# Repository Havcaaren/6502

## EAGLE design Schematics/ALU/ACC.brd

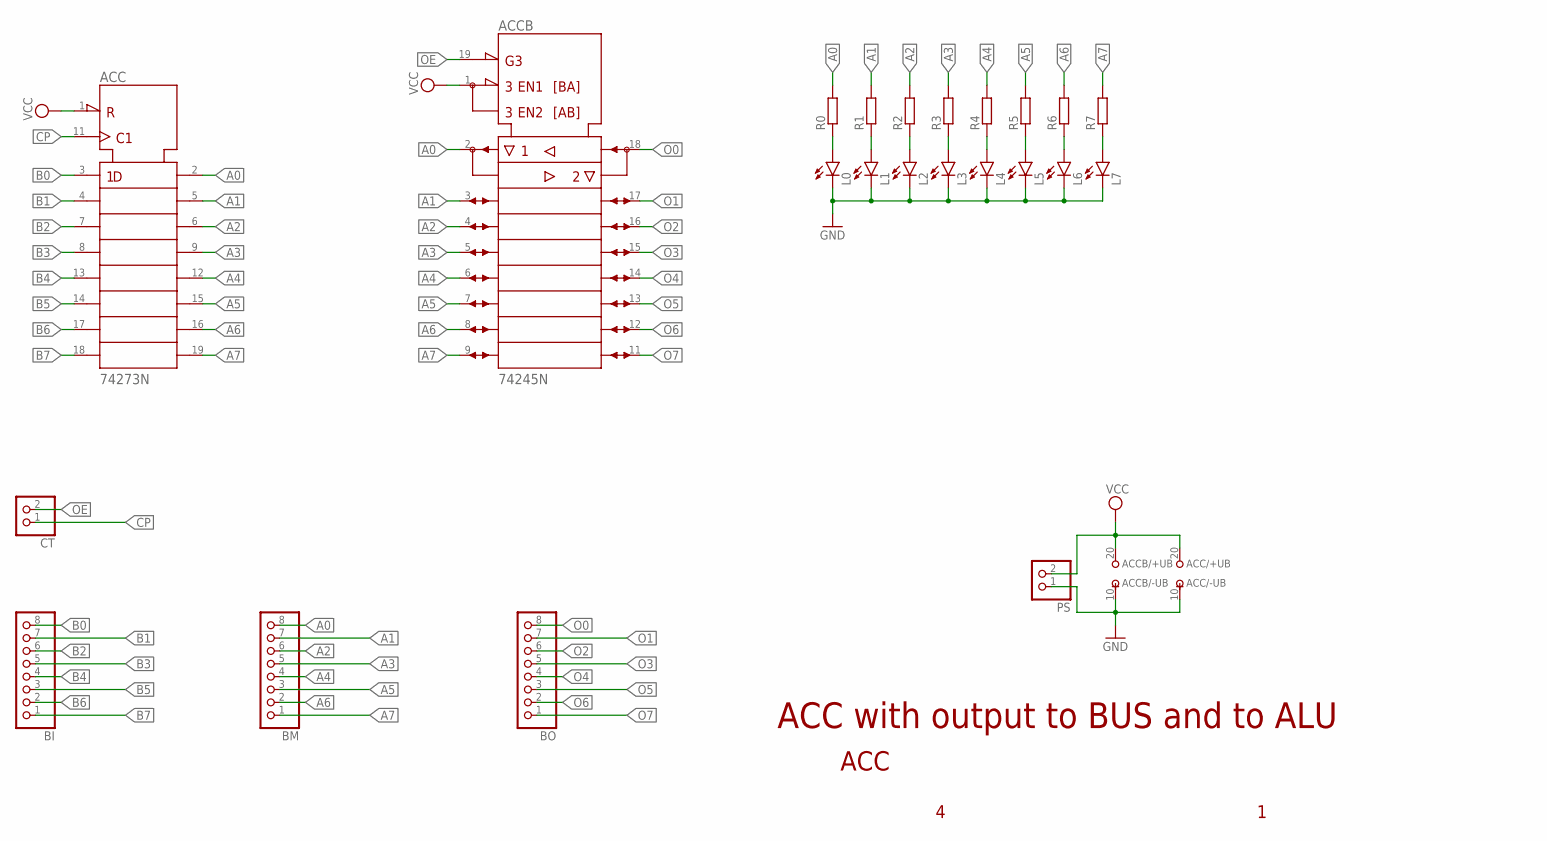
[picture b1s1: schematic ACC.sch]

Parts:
ACC: 74273N; DIL20
ACCB: 74245N; DIL20
BI: PINHD-1X8; 1X08
BM: PINHD-1X8; 1X08
BO: PINHD-1X8; 1X08
CT: PINHD-1X2; 1X02
L0, L1, L2, L3, L4, L5, L6, L7: LED5MM
PS: PINHD-1X2; 1X02
R0, R1, R2, R3, R4, R5, R6, R7: R-EU_0204/7; 0204/7

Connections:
A0: ACC.2 (1Q), ACCB.2 (A1), BM.8, R0.2
A1: ACC.5 (2Q), ACCB.3 (A2), BM.7, R1.2
A2: ACC.6 (3Q), ACCB.4 (A3), BM.6, R2.2
A3: ACC.9 (4Q), ACCB.5 (A4), BM.5, R3.2
A4: ACC.12 (5Q), ACCB.6 (A5), BM.4, R4.2
A5: ACC.15 (6Q), ACCB.7 (A6), BM.3, R5.2
A6: ACC.16 (7Q), ACCB.8 (A7), BM.2, R6.2
A7: ACC.19 (8Q), ACCB.9 (A8), BM.1, R7.2
B0: ACC.3 (1D), BI.8
B1: ACC.4 (2D), BI.7
B2: ACC.7 (3D), BI.6
B3: ACC.8 (4D), BI.5
B4: ACC.13 (5D), BI.4
B5: ACC.14 (6D), BI.3
B6: ACC.17 (7D), BI.2
B7: ACC.18 (8D), BI.1
CP: ACC.11 (CLK), CT.1
GND: ACC.10 (-UB), ACCB.10 (-UB), L0.K (C), L1.K (C), L2.K (C), L3.K (C), L4.K (C), L5.K (C), L6.K (C), L7.K (C), PS.1
unnamed: L0.A, R0.1
unnamed: L1.A, R1.1
unnamed: L2.A, R2.1
unnamed: L3.A, R3.1
unnamed: L4.A, R4.1
unnamed: L5.A, R5.1
unnamed: L6.A, R6.1
unnamed: L7.A, R7.1
O0: ACCB.18 (B1), BO.8
O1: ACCB.17 (B2), BO.7
O2: ACCB.16 (B3), BO.6
O3: ACCB.15 (B4), BO.5
O4: ACCB.14 (B5), BO.4
O5: ACCB.13 (B6), BO.3
O6: ACCB.12 (B7), BO.2
O7: ACCB.11 (B8), BO.1
OE: ACCB.19 (!G), CT.2
VCC: ACC.1 (!CLR), ACC.20 (+UB), ACCB.1 (DIR), ACCB.20 (+UB), PS.2

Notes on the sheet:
ACC with output to BUS and to ALU
ACC

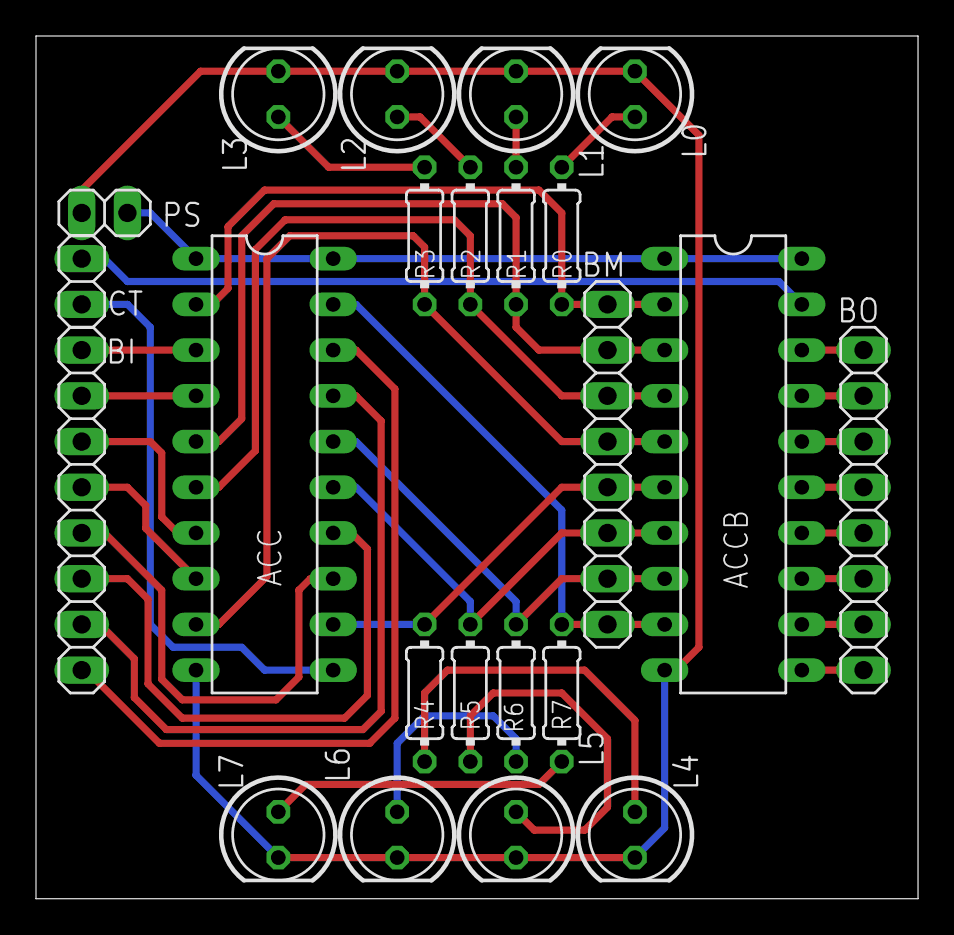
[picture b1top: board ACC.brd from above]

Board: 2 copper layers, 49.0 x 47.9 mm, 23 parts (0 on the bottom side), 36 nets.

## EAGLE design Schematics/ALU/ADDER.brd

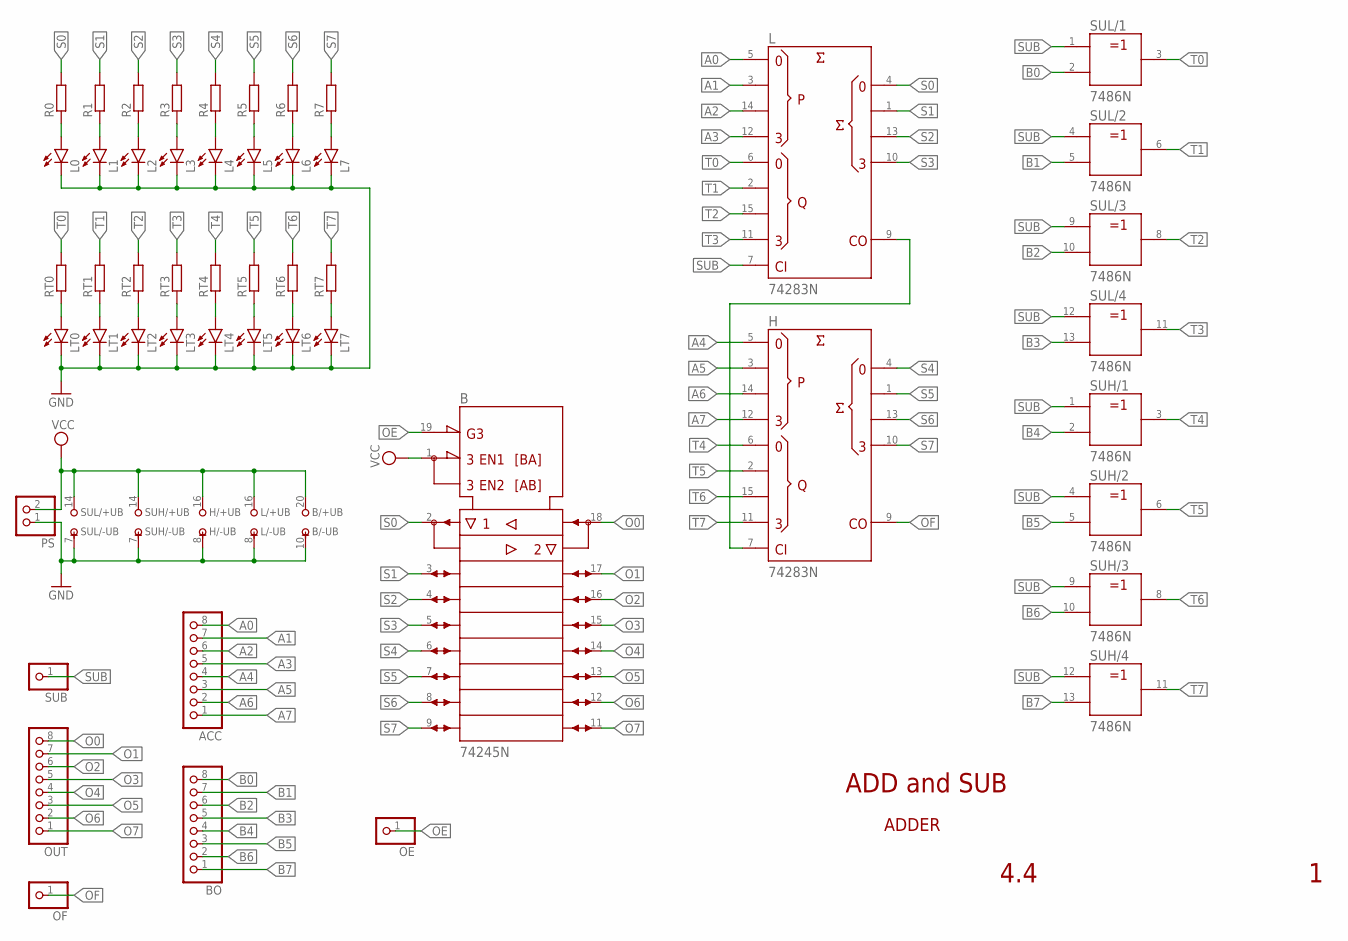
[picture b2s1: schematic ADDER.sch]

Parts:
ACC: PINHD-1X8; 1X08
B: 74245N; DIL20
BO: PINHD-1X8; 1X08
H: 74283N; DIL16
L: 74283N; DIL16
L0, L1, L2, L3, L4, L5, L6, L7: LED5MM
LT0, LT1, LT2, LT3, LT4, LT5, LT6, LT7: LED5MM
OE: PINHD-1X1; 1X01
OF: PINHD-1X1; 1X01
OUT: PINHD-1X8; 1X08
PS: PINHD-1X2; 1X02
R0, R1, R2, R3, R4, R5, R6, R7: R-EU_0204/7; 0204/7
RT0, RT1, RT2, RT3, RT4, RT5, RT6, RT7: R-EU_0204/7; 0204/7
SUB: PINHD-1X1; 1X01
SUH: 7486N; DIL14
SUL: 7486N; DIL14

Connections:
A0: ACC.8, L.5 (A1)
A1: ACC.7, L.3 (A2)
A2: ACC.6, L.14 (A3)
A3: ACC.5, L.12 (A4)
A4: ACC.4, H.5 (A1)
A5: ACC.3, H.3 (A2)
A6: ACC.2, H.14 (A3)
A7: ACC.1, H.12 (A4)
B0: BO.8, SUL.2 (B)
B1: BO.7, SUL.5 (B)
B2: BO.6, SUL.10 (B)
B3: BO.5, SUL.13 (B)
B4: BO.4, SUH.2 (B)
B5: BO.3, SUH.5 (B)
B6: BO.2, SUH.10 (B)
B7: BO.1, SUH.13 (B)
GND: B.10 (-UB), H.8 (-UB), L.8 (-UB), L0.K (C), L1.K (C), L2.K (C), L3.K (C), L4.K (C), L5.K (C), L6.K (C), L7.K (C), LT0.K (C), LT1.K (C), LT2.K (C), LT3.K (C), LT4.K (C), LT5.K (C), LT6.K (C), LT7.K (C), PS.1, SUH.7 (-UB), SUL.7 (-UB)
unnamed: H.7 (C0), L.9 (C4)
unnamed: L0.A, R0.1
unnamed: L1.A, R1.1
unnamed: L2.A, R2.1
unnamed: L3.A, R3.1
unnamed: L4.A, R4.1
unnamed: L5.A, R5.1
unnamed: L6.A, R6.1
unnamed: L7.A, R7.1
unnamed: LT0.A, RT0.1
unnamed: LT1.A, RT1.1
unnamed: LT2.A, RT2.1
unnamed: LT3.A, RT3.1
unnamed: LT4.A, RT4.1
unnamed: LT5.A, RT5.1
unnamed: LT6.A, RT6.1
unnamed: LT7.A, RT7.1
O0: B.18 (B1), OUT.8
O1: B.17 (B2), OUT.7
O2: B.16 (B3), OUT.6
O3: B.15 (B4), OUT.5
O4: B.14 (B5), OUT.4
O5: B.13 (B6), OUT.3
O6: B.12 (B7), OUT.2
O7: B.11 (B8), OUT.1
OE: B.19 (!G), OE.1
OF: H.9 (C4), OF.1
S0: B.2 (A1), L.4 (S1), R0.2
S1: B.3 (A2), L.1 (S2), R1.2
S2: B.4 (A3), L.13 (S3), R2.2
S3: B.5 (A4), L.10 (S4), R3.2
S4: B.6 (A5), H.4 (S1), R4.2
S5: B.7 (A6), H.1 (S2), R5.2
S6: B.8 (A7), H.13 (S3), R6.2
S7: B.9 (A8), H.10 (S4), R7.2
SUB: L.7 (C0), SUB.1, SUH.1 (A), SUH.4 (A), SUH.9 (A), SUH.12 (A), SUL.1 (A), SUL.4 (A), SUL.9 (A), SUL.12 (A)
T0: L.6 (B1), RT0.2, SUL.3 (Y)
T1: L.2 (B2), RT1.2, SUL.6 (Y)
T2: L.15 (B3), RT2.2, SUL.8 (Y)
T3: L.11 (B4), RT3.2, SUL.11 (Y)
T4: H.6 (B1), RT4.2, SUH.3 (Y)
T5: H.2 (B2), RT5.2, SUH.6 (Y)
T6: H.15 (B3), RT6.2, SUH.8 (Y)
T7: H.11 (B4), RT7.2, SUH.11 (Y)
VCC: B.1 (DIR), B.20 (+UB), H.16 (+UB), L.16 (+UB), PS.2, SUH.14 (+UB), SUL.14 (+UB)

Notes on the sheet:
ADD and SUB
ADDER
4.4

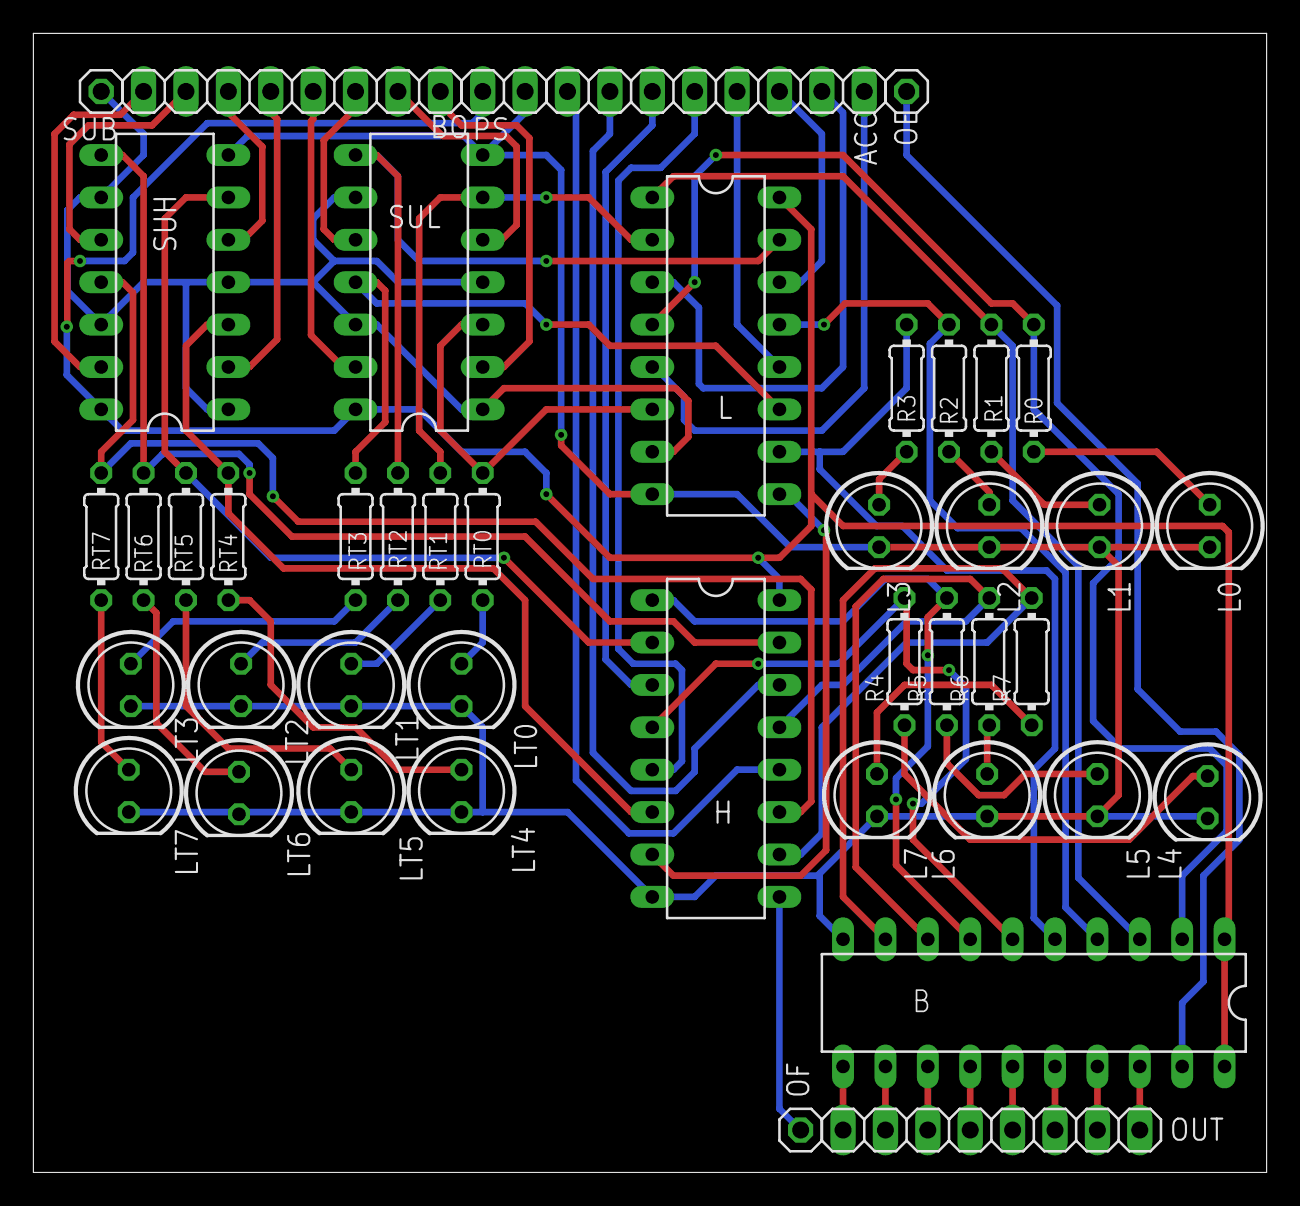
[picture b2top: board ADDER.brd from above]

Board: 2 copper layers, 73.9 x 68.2 mm, 44 parts (0 on the bottom side), 62 nets.

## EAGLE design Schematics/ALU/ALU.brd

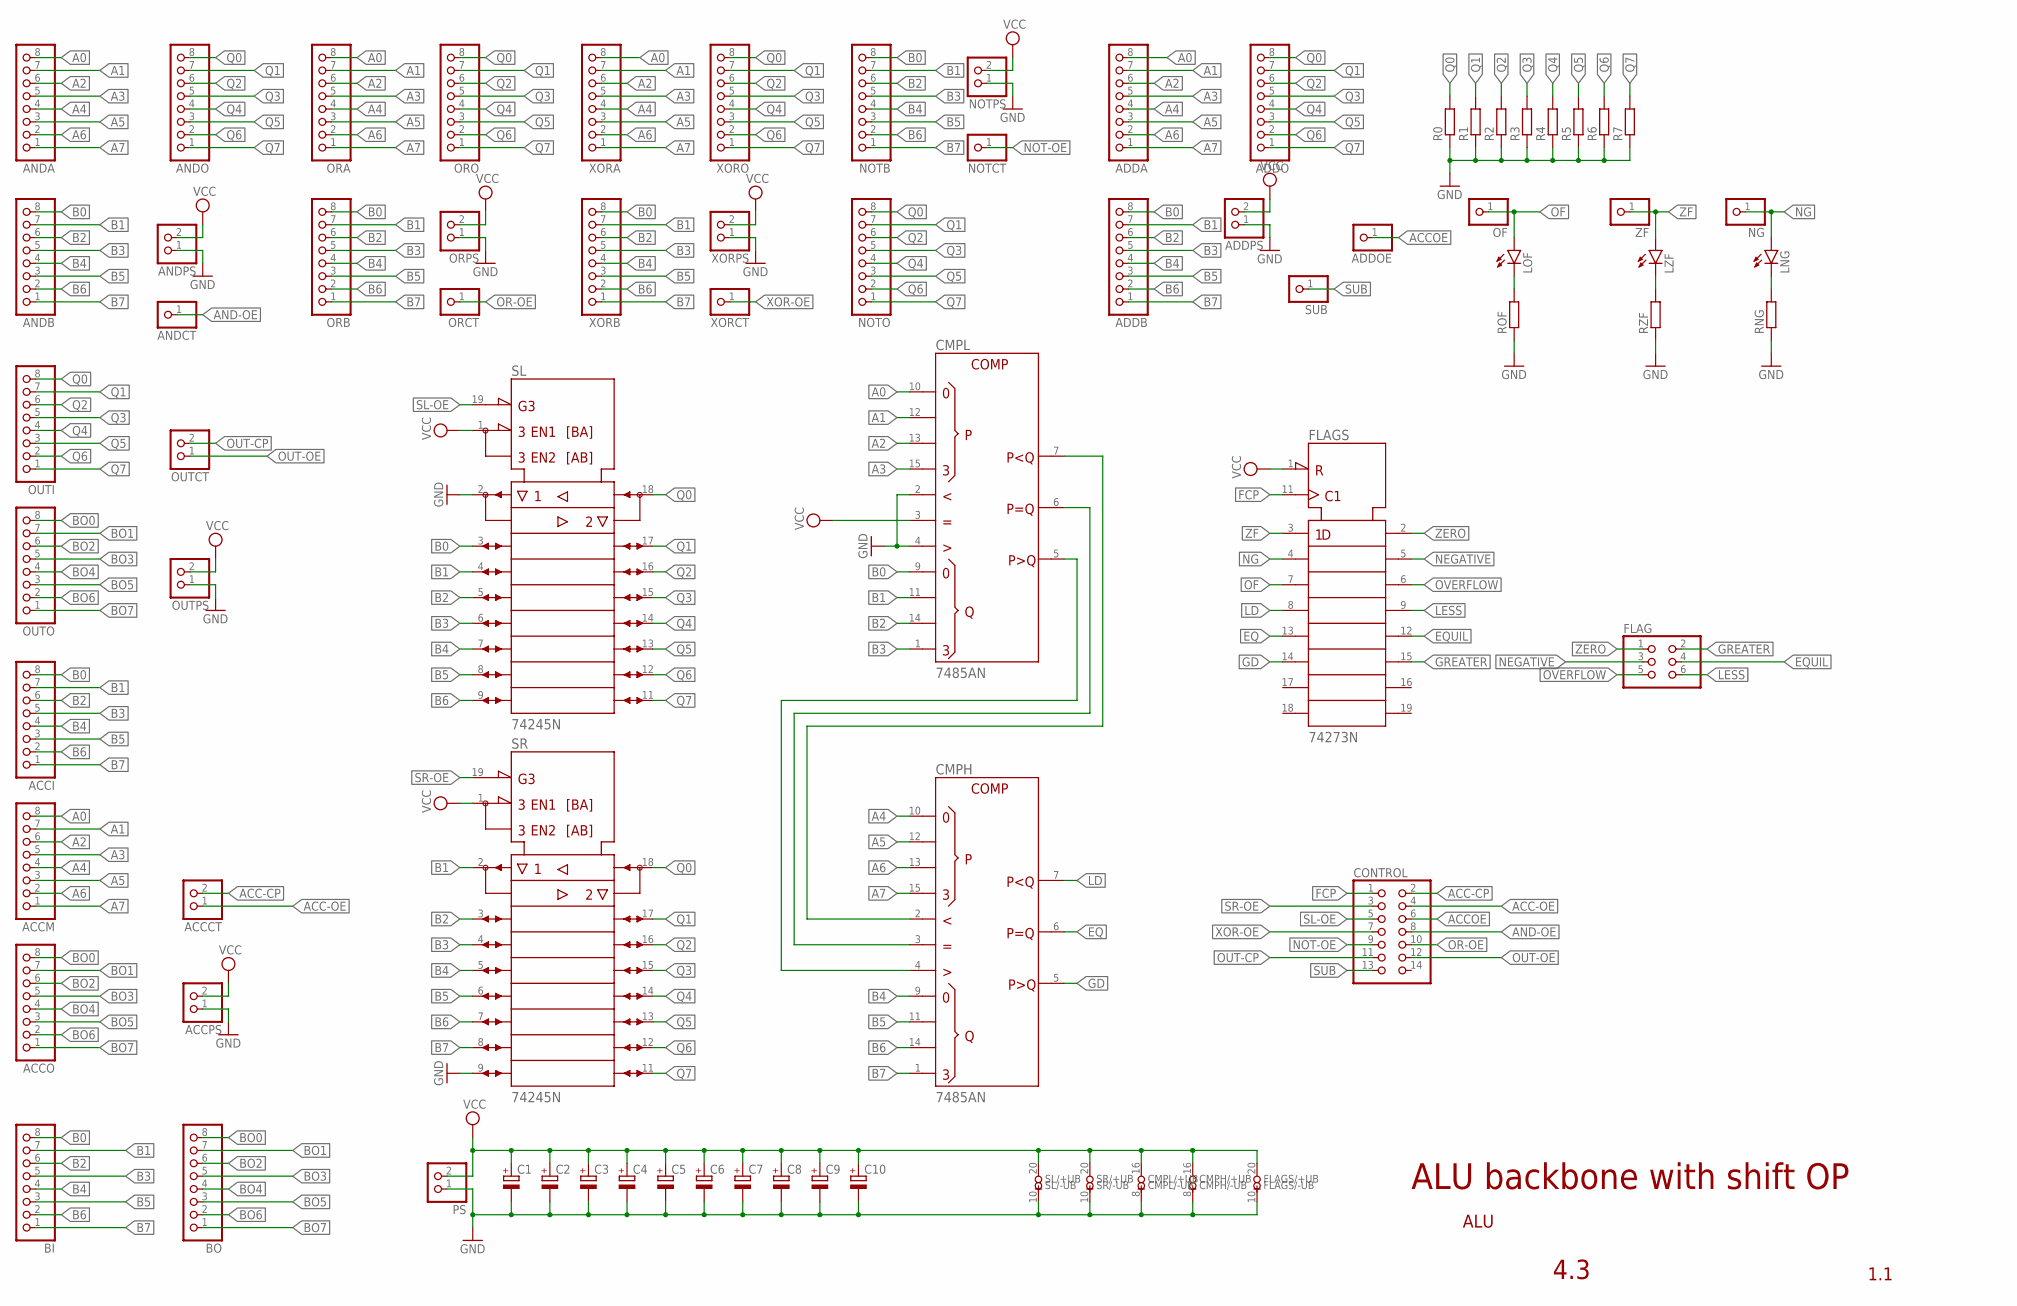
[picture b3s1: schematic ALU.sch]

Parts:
ACCCT: PINHD-1X2; 1X02
ACCI: PINHD-1X8; 1X08
ACCM: PINHD-1X8; 1X08
ACCO: PINHD-1X8; 1X08
ACCPS: PINHD-1X2; 1X02
ADDA: PINHD-1X8; 1X08
ADDB: PINHD-1X8; 1X08
ADDO: PINHD-1X8; 1X08
ADDOE: PINHD-1X1; 1X01
ADDPS: PINHD-1X2; 1X02
ANDA: PINHD-1X8; 1X08
ANDB: PINHD-1X8; 1X08
ANDCT: PINHD-1X1; 1X01
ANDO: PINHD-1X8; 1X08
ANDPS: PINHD-1X2; 1X02
BI: PINHD-1X8; 1X08
BO: PINHD-1X8; 1X08
C1, C2, C3, C4, C5, C6, C7, C8, C9, C10: CPOL-EUE2.5-6; E2,5-6
CMPH: 7485AN; DIL16
CMPL: 7485AN; DIL16
CONTROL: PINHD-2X7; 2X07
FLAG: PINHD-2X3; 2X03
FLAGS: 74273N; DIL20
LNG: LED5MM
LOF: LED5MM
LZF: LED5MM
NG: PINHD-1X1; 1X01
NOTB: PINHD-1X8; 1X08
NOTCT: PINHD-1X1; 1X01
NOTO: PINHD-1X8; 1X08
NOTPS: PINHD-1X2; 1X02
OF: PINHD-1X1; 1X01
ORA: PINHD-1X8; 1X08
ORB: PINHD-1X8; 1X08
ORCT: PINHD-1X1; 1X01
ORO: PINHD-1X8; 1X08
ORPS: PINHD-1X2; 1X02
OUTCT: PINHD-1X2; 1X02
OUTI: PINHD-1X8; 1X08
OUTO: PINHD-1X8; 1X08
OUTPS: PINHD-1X2; 1X02
PS: PINHD-1X2; 1X02
R0, R1, R2, R3, R4, R5, R6, R7: R-EU_0204/7; 0204/7
RNG: R-EU_0204/7; 0204/7
ROF: R-EU_0204/7; 0204/7
RZF: R-EU_0204/7; 0204/7
SL: 74245N; DIL20
SR: 74245N; DIL20
SUB: PINHD-1X1; 1X01
XORA: PINHD-1X8; 1X08
XORB: PINHD-1X8; 1X08
XORCT: PINHD-1X1; 1X01
XORO: PINHD-1X8; 1X08
XORPS: PINHD-1X2; 1X02
ZF: PINHD-1X1; 1X01

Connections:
A0: ACCM.8, ADDA.8, ANDA.8, CMPL.10 (P0), ORA.8, XORA.8
A1: ACCM.7, ADDA.7, ANDA.7, CMPL.12 (P1), ORA.7, XORA.7
A2: ACCM.6, ADDA.6, ANDA.6, CMPL.13 (P2), ORA.6, XORA.6
A3: ACCM.5, ADDA.5, ANDA.5, CMPL.15 (P3), ORA.5, XORA.5
A4: ACCM.4, ADDA.4, ANDA.4, CMPH.10 (P0), ORA.4, XORA.4
A5: ACCM.3, ADDA.3, ANDA.3, CMPH.12 (P1), ORA.3, XORA.3
A6: ACCM.2, ADDA.2, ANDA.2, CMPH.13 (P2), ORA.2, XORA.2
A7: ACCM.1, ADDA.1, ANDA.1, CMPH.15 (P3), ORA.1, XORA.1
ACC-CP: ACCCT.2, CONTROL.2
ACC-OE: ACCCT.1, CONTROL.4
ACCOE: ADDOE.1, CONTROL.6
AND-OE: ANDCT.1, CONTROL.8
B0: ACCI.8, ADDB.8, ANDB.8, BI.8, CMPL.9 (Q0), NOTB.8, ORB.8, SL.3 (A2), XORB.8
B1: ACCI.7, ADDB.7, ANDB.7, BI.7, CMPL.11 (Q1), NOTB.7, ORB.7, SL.4 (A3), SR.2 (A1), XORB.7
B2: ACCI.6, ADDB.6, ANDB.6, BI.6, CMPL.14 (Q2), NOTB.6, ORB.6, SL.5 (A4), SR.3 (A2), XORB.6
B3: ACCI.5, ADDB.5, ANDB.5, BI.5, CMPL.1 (Q3), NOTB.5, ORB.5, SL.6 (A5), SR.4 (A3), XORB.5
B4: ACCI.4, ADDB.4, ANDB.4, BI.4, CMPH.9 (Q0), NOTB.4, ORB.4, SL.7 (A6), SR.5 (A4), XORB.4
B5: ACCI.3, ADDB.3, ANDB.3, BI.3, CMPH.11 (Q1), NOTB.3, ORB.3, SL.8 (A7), SR.6 (A5), XORB.3
B6: ACCI.2, ADDB.2, ANDB.2, BI.2, CMPH.14 (Q2), NOTB.2, ORB.2, SL.9 (A8), SR.7 (A6), XORB.2
B7: ACCI.1, ADDB.1, ANDB.1, BI.1, CMPH.1 (Q3), NOTB.1, ORB.1, SR.8 (A7), XORB.1
BO0: ACCO.8, BO.8, OUTO.8
BO1: ACCO.7, BO.7, OUTO.7
BO2: ACCO.6, BO.6, OUTO.6
BO3: ACCO.5, BO.5, OUTO.5
BO4: ACCO.4, BO.4, OUTO.4
BO5: ACCO.3, BO.3, OUTO.3
BO6: ACCO.2, BO.2, OUTO.2
BO7: ACCO.1, BO.1, OUTO.1
EQ: CMPH.6 (PEQQ), FLAGS.13 (5D)
EQUIL: FLAG.4, FLAGS.12 (5Q)
FCP: CONTROL.1, FLAGS.11 (CLK)
GD: CMPH.5 (PGTQ), FLAGS.14 (6D)
GND: ACCPS.1, ADDPS.1, ANDPS.1, C1.-, C2.-, C3.-, C4.-, C5.-, C6.-, C7.-, C8.-, C9.-, C10.-, CMPH.8 (-UB), CMPL.2 (PLTQ_), CMPL.4 (PGTQ_), CMPL.8 (-UB), FLAGS.10 (-UB), NOTPS.1, ORPS.1, OUTPS.1, PS.1, R0.1, R1.1, R2.1, R3.1, R4.1, R5.1, R6.1, R7.1, RNG.1, ROF.1, RZF.1, SL.2 (A1), SL.10 (-UB), SR.9 (A8), SR.10 (-UB), XORPS.1
GREATER: FLAG.2, FLAGS.15 (6Q)
LD: CMPH.7 (PLTQ), FLAGS.8 (4D)
LESS: FLAG.6, FLAGS.9 (4Q)
unnamed: LOF.K (C), ROF.2
unnamed: LZF.K (C), RZF.2
unnamed: LNG.K (C), RNG.2
unnamed: CMPH.4 (PGTQ_), CMPL.5 (PGTQ)
unnamed: CMPH.3 (PEQQ_), CMPL.6 (PEQQ)
unnamed: CMPH.2 (PLTQ_), CMPL.7 (PLTQ)
NEGATIVE: FLAG.3, FLAGS.5 (2Q)
NG: FLAGS.4 (2D), LNG.A, NG.1
NOT-OE: CONTROL.9, NOTCT.1
OF: FLAGS.7 (3D), LOF.A, OF.1
OR-OE: CONTROL.10, ORCT.1
OUT-CP: CONTROL.11, OUTCT.2
OUT-OE: CONTROL.12, OUTCT.1
OVERFLOW: FLAG.5, FLAGS.6 (3Q)
Q0: ADDO.8, ANDO.8, NOTO.8, ORO.8, OUTI.8, R0.2, SL.18 (B1), SR.18 (B1), XORO.8
Q1: ADDO.7, ANDO.7, NOTO.7, ORO.7, OUTI.7, R1.2, SL.17 (B2), SR.17 (B2), XORO.7
Q2: ADDO.6, ANDO.6, NOTO.6, ORO.6, OUTI.6, R2.2, SL.16 (B3), SR.16 (B3), XORO.6
Q3: ADDO.5, ANDO.5, NOTO.5, ORO.5, OUTI.5, R3.2, SL.15 (B4), SR.15 (B4), XORO.5
Q4: ADDO.4, ANDO.4, NOTO.4, ORO.4, OUTI.4, R4.2, SL.14 (B5), SR.14 (B5), XORO.4
Q5: ADDO.3, ANDO.3, NOTO.3, ORO.3, OUTI.3, R5.2, SL.13 (B6), SR.13 (B6), XORO.3
Q6: ADDO.2, ANDO.2, NOTO.2, ORO.2, OUTI.2, R6.2, SL.12 (B7), SR.12 (B7), XORO.2
Q7: ADDO.1, ANDO.1, NOTO.1, ORO.1, OUTI.1, R7.2, SL.11 (B8), SR.11 (B8), XORO.1
SL-OE: CONTROL.5, SL.19 (!G)
SR-OE: CONTROL.3, SR.19 (!G)
SUB: CONTROL.13, SUB.1
VCC: ACCPS.2, ADDPS.2, ANDPS.2, C1.+, C2.+, C3.+, C4.+, C5.+, C6.+, C7.+, C8.+, C9.+, C10.+, CMPH.16 (+UB), CMPL.3 (PEQQ_), CMPL.16 (+UB), FLAGS.1 (!CLR), FLAGS.20 (+UB), NOTPS.2, ORPS.2, OUTPS.2, PS.2, SL.1 (DIR), SL.20 (+UB), SR.1 (DIR), SR.20 (+UB), XORPS.2
XOR-OE: CONTROL.7, XORCT.1
ZERO: FLAG.1, FLAGS.2 (1Q)
ZF: FLAGS.3 (1D), LZF.A, ZF.1

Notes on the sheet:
1.1
4.3
ALU
ALU backbone with shift OP

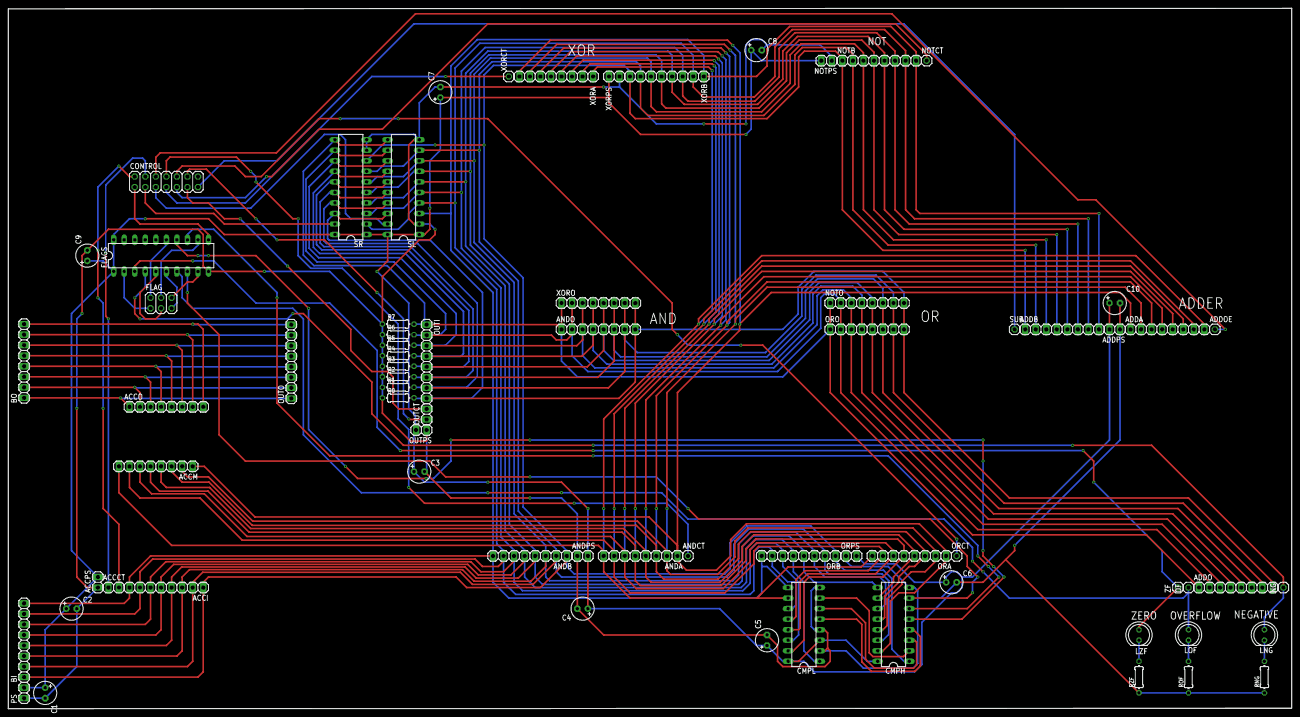
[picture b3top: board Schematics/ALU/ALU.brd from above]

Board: 2 copper layers, 309.4 x 168.8 mm, 71 parts (0 on the bottom side), 65 nets.

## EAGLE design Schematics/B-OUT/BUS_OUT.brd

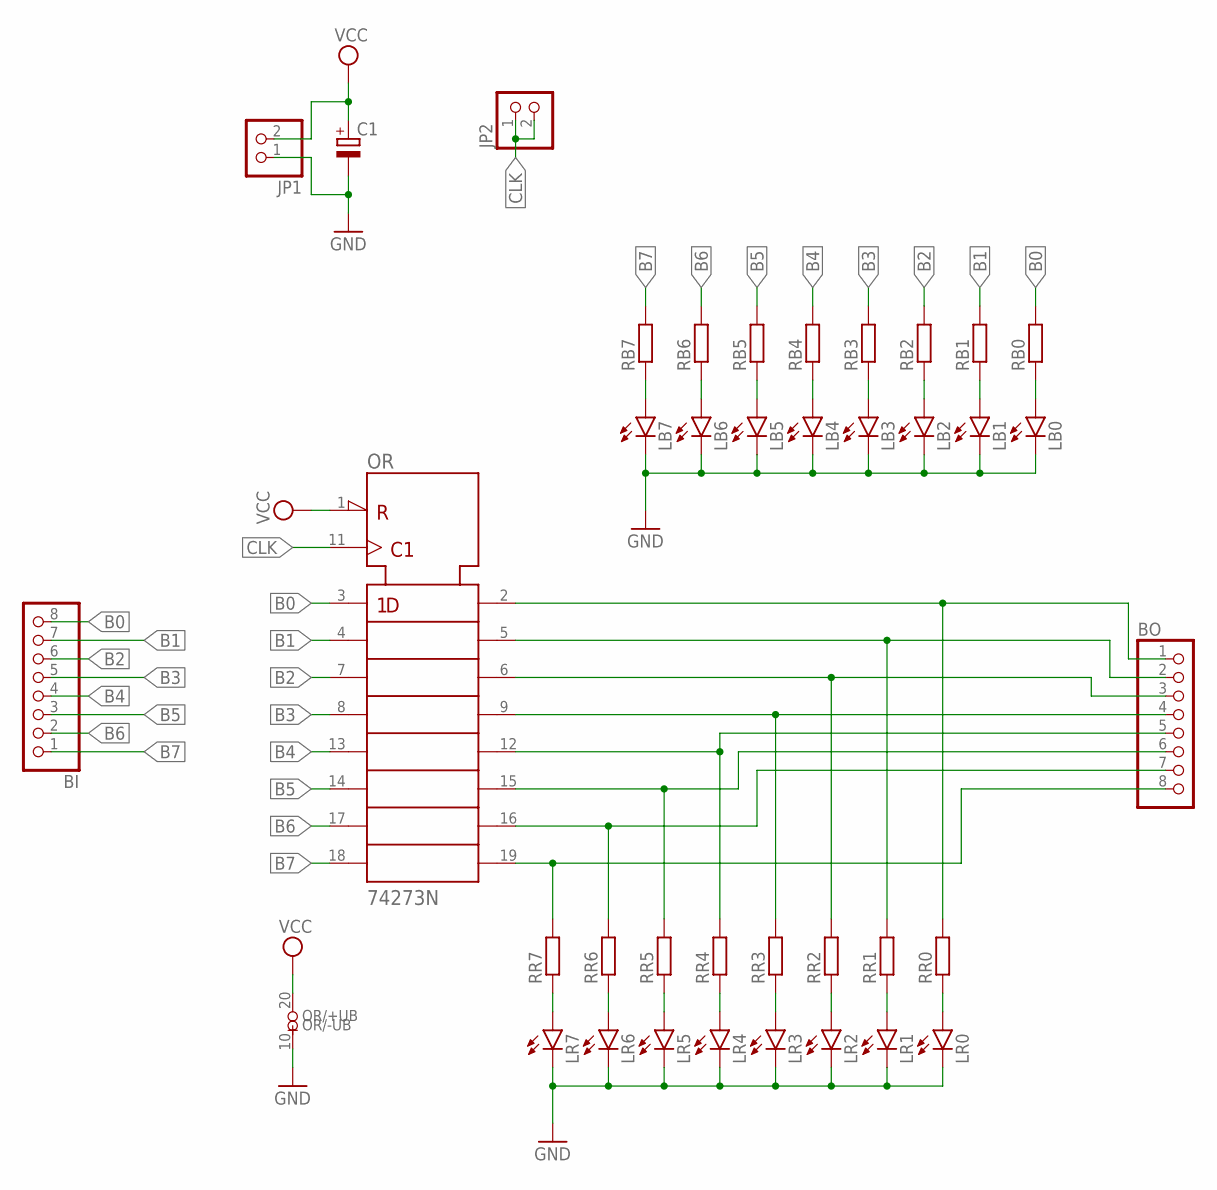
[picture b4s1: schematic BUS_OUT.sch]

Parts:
BI: PINHD-1X8; 1X08
BO: PINHD-1X8; 1X08
C1: CPOL-EUE2.5-6; E2,5-6
JP1, JP2: PINHD-1X2; 1X02
LB0, LB1, LB2, LB3, LB4, LB5, LB6, LB7: LED5MM
LR0, LR1, LR2, LR3, LR4, LR5, LR6, LR7: LED5MM
OR: 74273N; DIL20
RB0, RB1, RB2, RB3, RB4, RB5, RB6, RB7: R-EU_0204/7; 0204/7
RR0, RR1, RR2, RR3, RR4, RR5, RR6, RR7: R-EU_0204/7; 0204/7

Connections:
B0: BI.8, OR.3 (1D), RB0.2
B1: BI.7, OR.4 (2D), RB1.2
B2: BI.6, OR.7 (3D), RB2.2
B3: BI.5, OR.8 (4D), RB3.2
B4: BI.4, OR.13 (5D), RB4.2
B5: BI.3, OR.14 (6D), RB5.2
B6: BI.2, OR.17 (7D), RB6.2
B7: BI.1, OR.18 (8D), RB7.2
CLK: JP2.1, JP2.2, OR.11 (CLK)
GND: C1.-, JP1.1, LB0.K (C), LB1.K (C), LB2.K (C), LB3.K (C), LB4.K (C), LB5.K (C), LB6.K (C), LB7.K (C), LR0.K (C), LR1.K (C), LR2.K (C), LR3.K (C), LR4.K (C), LR5.K (C), LR6.K (C), LR7.K (C), OR.10 (-UB)
unnamed: LB7.A, RB7.1
unnamed: LB6.A, RB6.1
unnamed: LB5.A, RB5.1
unnamed: LB4.A, RB4.1
unnamed: LR7.A, RR7.1
unnamed: LB3.A, RB3.1
unnamed: BO.8, OR.19 (8Q), RR7.2
unnamed: LR6.A, RR6.1
unnamed: BO.7, OR.16 (7Q), RR6.2
unnamed: LR5.A, RR5.1
unnamed: LB2.A, RB2.1
unnamed: BO.6, OR.15 (6Q), RR5.2
unnamed: LR4.A, RR4.1
unnamed: BO.5, OR.12 (5Q), RR4.2
unnamed: LR3.A, RR3.1
unnamed: LB1.A, RB1.1
unnamed: BO.4, OR.9 (4Q), RR3.2
unnamed: LR2.A, RR2.1
unnamed: BO.3, OR.6 (3Q), RR2.2
unnamed: LR1.A, RR1.1
unnamed: LB0.A, RB0.1
unnamed: BO.2, OR.5 (2Q), RR1.2
unnamed: LR0.A, RR0.1
unnamed: BO.1, OR.2 (1Q), RR0.2
VCC: C1.+, JP1.2, OR.1 (!CLR), OR.20 (+UB)

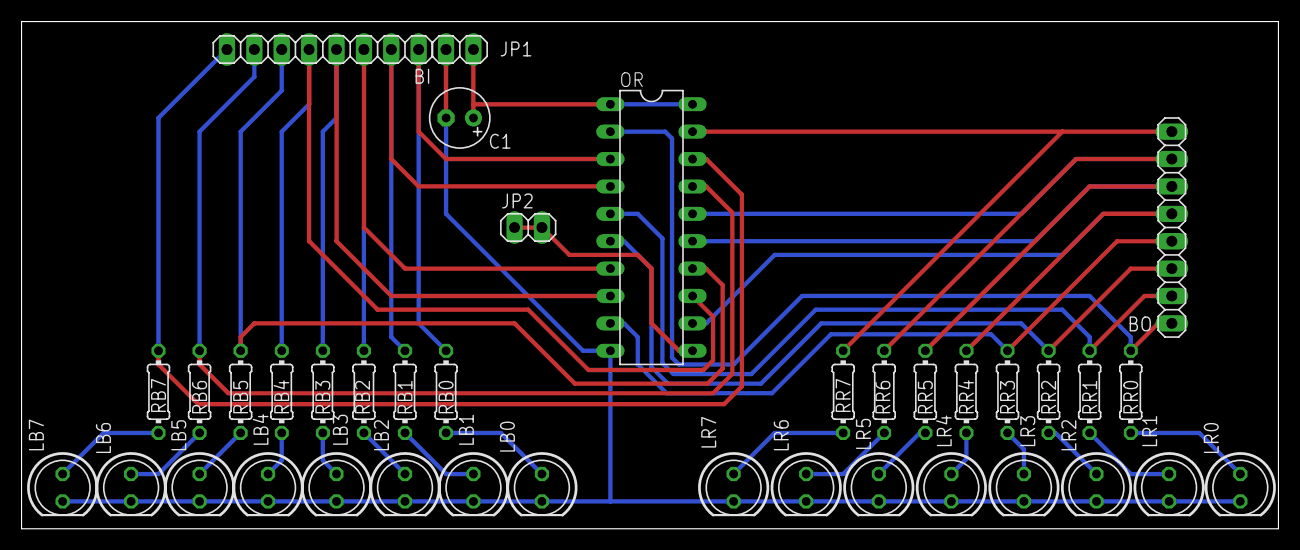
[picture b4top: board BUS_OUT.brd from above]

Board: 2 copper layers, 116.6 x 47.0 mm, 38 parts (0 on the bottom side), 35 nets.

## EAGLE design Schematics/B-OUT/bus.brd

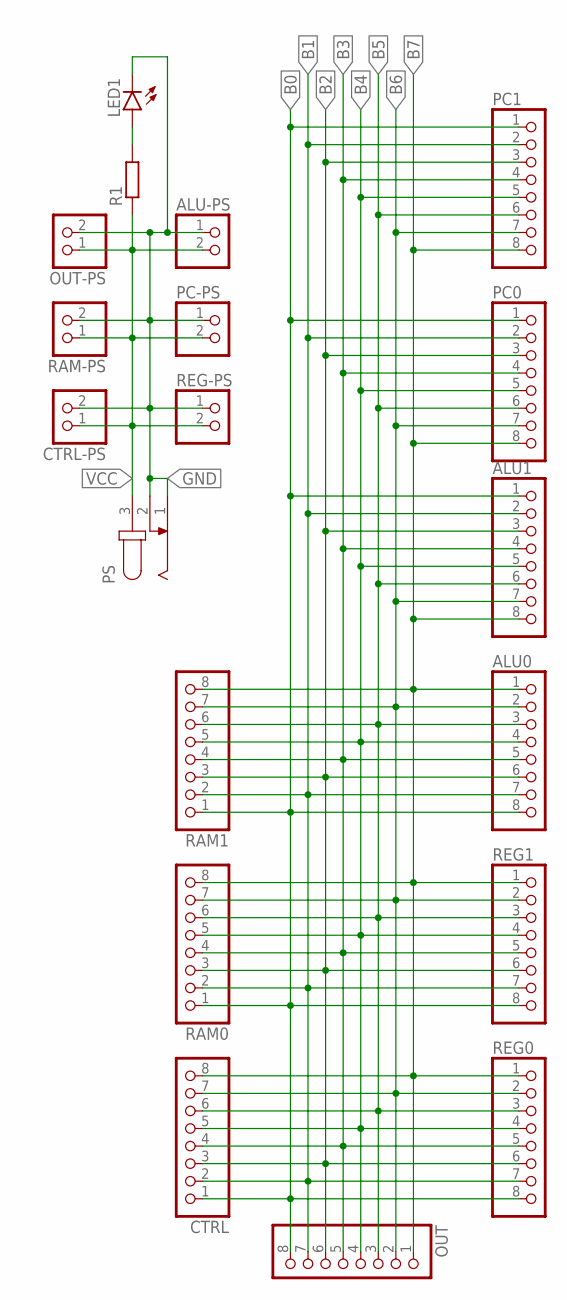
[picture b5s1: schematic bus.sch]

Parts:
ALU0, ALU1: PINHD-1X8; 1X08
ALU-PS: PINHD-1X2; 1X02
CTRL: PINHD-1X8; 1X08
CTRL-PS: PINHD-1X2; 1X02
LED1: LED5MM
OUT: PINHD-1X8; 1X08
OUT-PS: PINHD-1X2; 1X02
PC0, PC1: PINHD-1X8; 1X08
PC-PS: PINHD-1X2; 1X02
PS: JACK-PLUG0; SPC4077
R1: R-EU_0204/7; 0204/7
RAM0, RAM1: PINHD-1X8; 1X08
RAM-PS: PINHD-1X2; 1X02
REG0, REG1: PINHD-1X8; 1X08
REG-PS: PINHD-1X2; 1X02

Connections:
B0: ALU0.8, ALU1.1, CTRL.1, OUT.8, PC0.1, PC1.1, RAM0.1, RAM1.1, REG0.8, REG1.8
B1: ALU0.7, ALU1.2, CTRL.2, OUT.7, PC0.2, PC1.2, RAM0.2, RAM1.2, REG0.7, REG1.7
B2: ALU0.6, ALU1.3, CTRL.3, OUT.6, PC0.3, PC1.3, RAM0.3, RAM1.3, REG0.6, REG1.6
B3: ALU0.5, ALU1.4, CTRL.4, OUT.5, PC0.4, PC1.4, RAM0.4, RAM1.4, REG0.5, REG1.5
B4: ALU0.4, ALU1.5, CTRL.5, OUT.4, PC0.5, PC1.5, RAM0.5, RAM1.5, REG0.4, REG1.4
B5: ALU0.3, ALU1.6, CTRL.6, OUT.3, PC0.6, PC1.6, RAM0.6, RAM1.6, REG0.3, REG1.3
B6: ALU0.2, ALU1.7, CTRL.7, OUT.2, PC0.7, PC1.7, RAM0.7, RAM1.7, REG0.2, REG1.2
B7: ALU0.1, ALU1.8, CTRL.8, OUT.1, PC0.8, PC1.8, RAM0.8, RAM1.8, REG0.1, REG1.1
GND: ALU-PS.1, CTRL-PS.2, LED1.K (C), OUT-PS.2, PC-PS.1, PS.1, PS.2, RAM-PS.2, REG-PS.1
unnamed: LED1.A, R1.2
VCC: ALU-PS.2, CTRL-PS.1, OUT-PS.1, PC-PS.2, PS.3, R1.1, RAM-PS.1, REG-PS.2

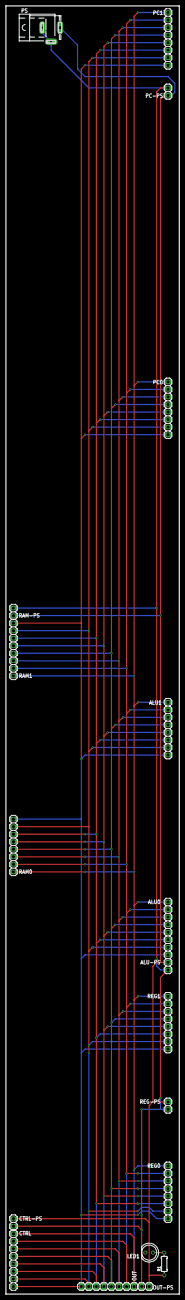
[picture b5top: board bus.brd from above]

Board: 2 copper layers, 58.4 x 434.0 mm, 19 parts (0 on the bottom side), 11 nets.
